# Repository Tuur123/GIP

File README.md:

# GIP
Luchtkwaliteit

Geïntegreede proef van Arthur d'Hooge en Ruben Socquet

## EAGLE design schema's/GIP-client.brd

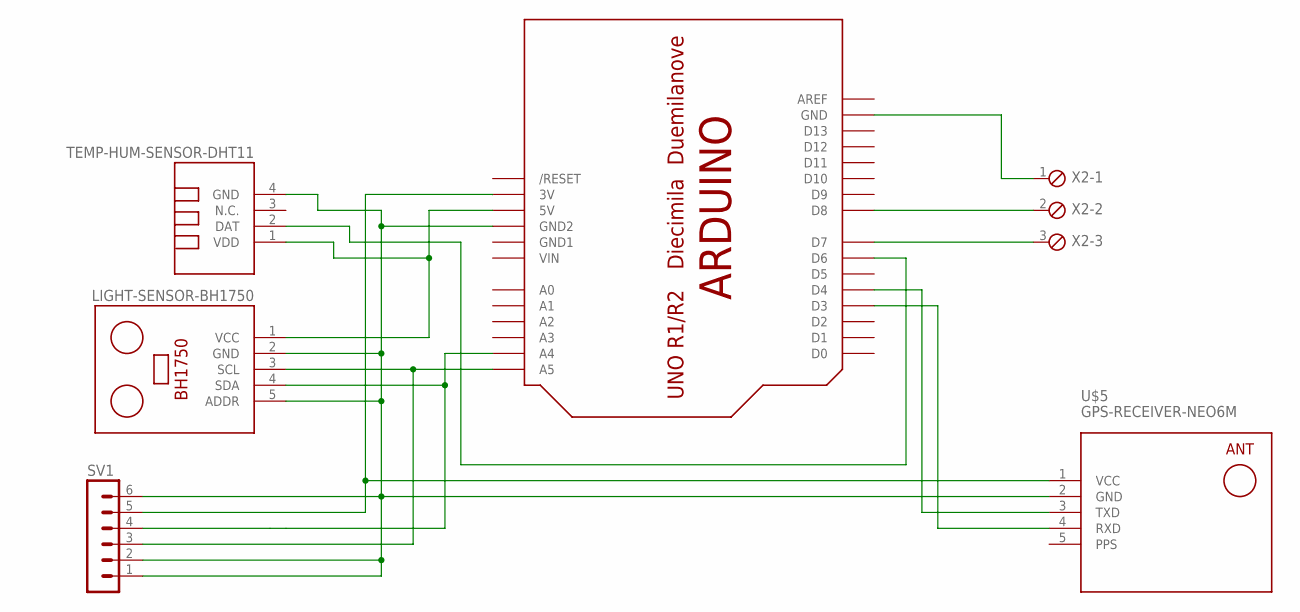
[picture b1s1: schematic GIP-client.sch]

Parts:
SV1: MA06-1
U$2: ARDUINO-BPLACE
U$3: TEMP-HUM-SENSOR-DHT11
U$4: LIGHT-SENSOR-BH1750
U$5: GPS-RECEIVER-NEO6M
X2: MPT3; 3POL254

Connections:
GND1: U$2.GND1
unnamed: U$2.GND, X2.1
unnamed: U$2.D8, X2.2
unnamed: U$2.D7, X2.3
unnamed: SV1.1, SV1.2, SV1.6, U$2.GND2, U$3.4 (GND), U$4.2 (GND), U$4.5 (ADDR), U$5.2 (GND)
unnamed: U$2.D6, U$3.2 (DAT)
unnamed: SV1.4, U$2.A4, U$4.4 (SDA)
unnamed: SV1.3, U$2.A5, U$4.3 (SCL)
unnamed: U$2.5V, U$3.1 (VDD), U$4.1 (VCC)
unnamed: SV1.5, U$2.3V, U$5.1 (VCC)
unnamed: U$2.D4, U$5.3 (TXD)
unnamed: U$2.D3, U$5.4 (RXD)
PPS: U$5.5 (PPS)
VIN: U$2.VIN

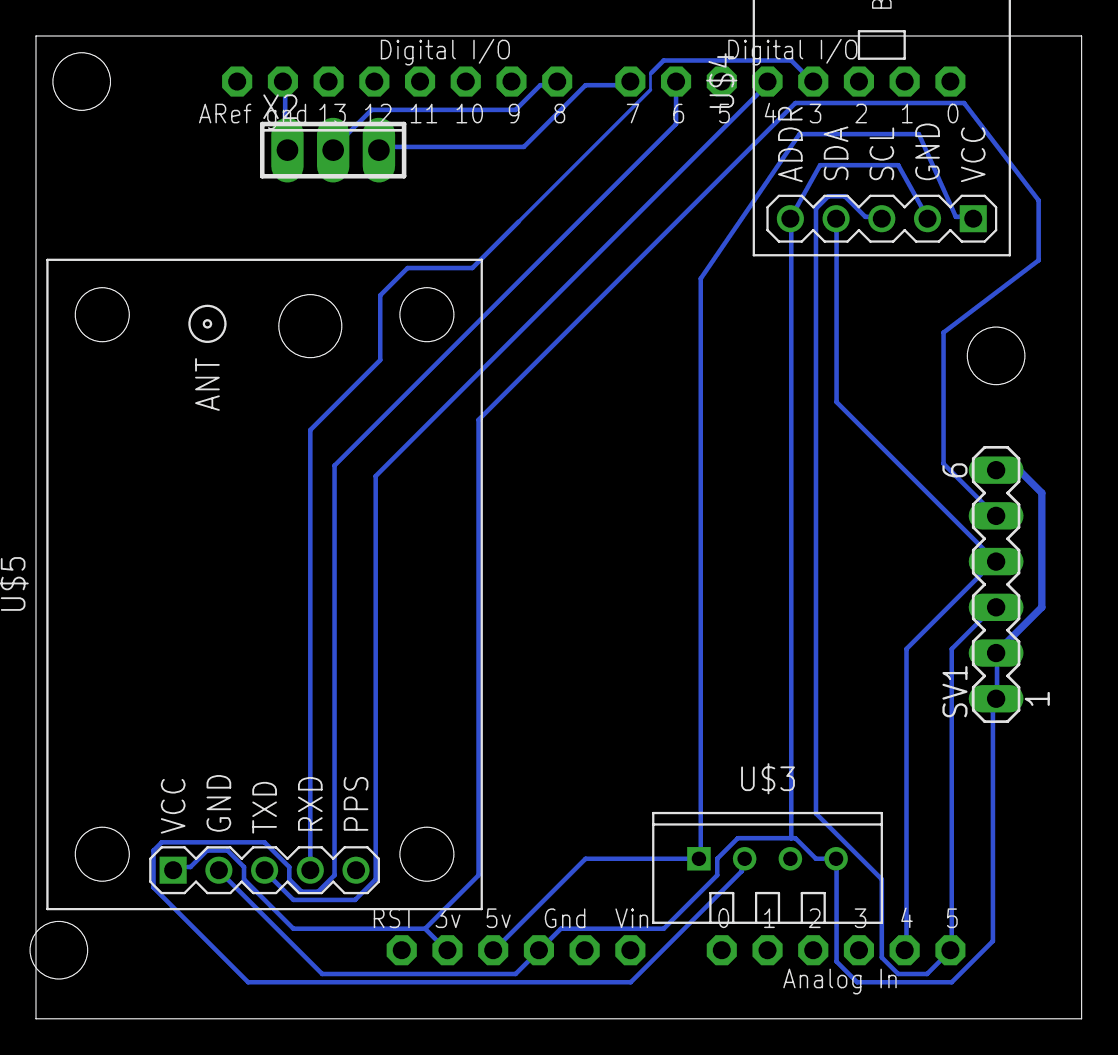
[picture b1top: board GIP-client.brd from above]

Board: 2 copper layers, 58.1 x 54.6 mm, 6 parts (0 on the bottom side), 11 nets.

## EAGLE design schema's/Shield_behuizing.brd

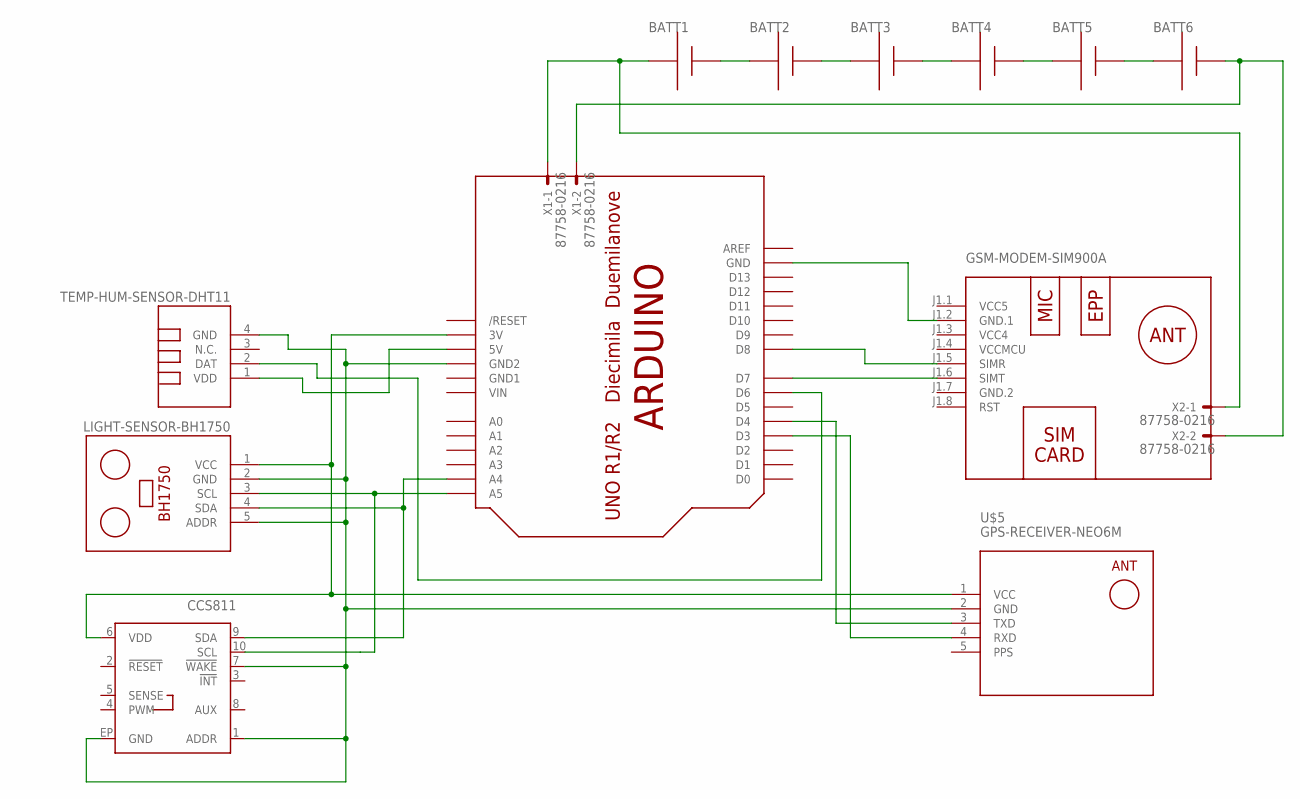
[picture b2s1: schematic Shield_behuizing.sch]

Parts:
BATT1, BATT2, BATT3, BATT4, BATT5, BATT6: AAA; 12BH412
U1: CCS811; LGA10
U$1: GSM-MODEM-SIM900A
U$2: ARDUINO-BPLACE
U$3: TEMP-HUM-SENSOR-DHT11
U$4: LIGHT-SENSOR-BH1750
U$5: GPS-RECEIVER-NEO6M
X1, X2: 87758-0216

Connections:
GND1: U$2.GND1
GND.2: U$1.J1.7 (GND.2)
unnamed: U$1.J1.2 (GND.1), U$2.GND
unnamed: U$1.J1.5 (SIMR), U$2.D8
unnamed: U$1.J1.6 (SIMT), U$2.D7
unnamed: BATT1.+, BATT2.-
unnamed: U1.1 (ADDR), U1.7 (!WAKE!), U1.EP (GND), U$2.GND2, U$3.4 (GND), U$4.2 (GND), U$4.5 (ADDR), U$5.2 (GND)
unnamed: U$2.D6, U$3.2 (DAT)
unnamed: U1.9 (SDA), U$2.A4, U$4.4 (SDA)
unnamed: U1.10 (SCL), U$2.A5, U$4.3 (SCL)
unnamed: U$2.5V, U$3.1 (VDD)
unnamed: BATT2.+, BATT3.-
unnamed: BATT3.+, BATT4.-
unnamed: BATT4.+, BATT5.-
unnamed: BATT5.+, BATT6.-
unnamed: U1.6 (VDD), U$2.3V, U$4.1 (VCC), U$5.1 (VCC)
unnamed: U$2.D4, U$5.3 (TXD)
unnamed: BATT1.-, X1.1, X2.1
unnamed: BATT6.+, X1.2, X2.2
unnamed: U$2.D3, U$5.4 (RXD)
PPS: U$5.5 (PPS)
VCC4: U$1.J1.3 (VCC4)
VCC5: U$1.J1.1 (VCC5)
VCCMCU: U$1.J1.4 (VCCMCU)
VIN: U$2.VIN

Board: 2 copper layers, 14 parts (0 on the bottom side), 18 nets, no tracks yet.

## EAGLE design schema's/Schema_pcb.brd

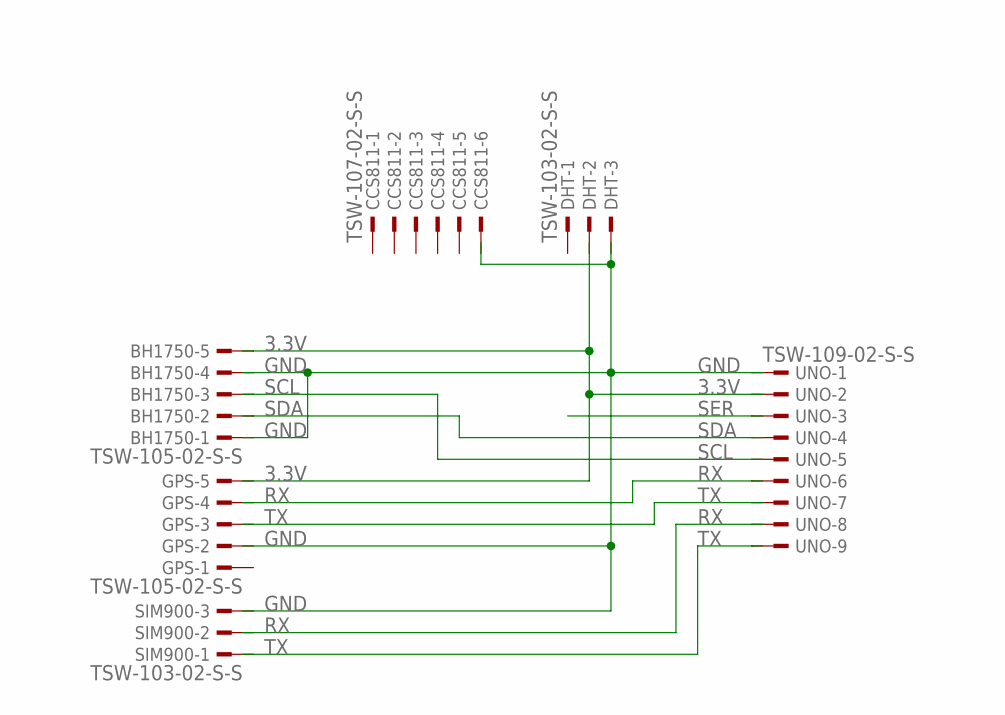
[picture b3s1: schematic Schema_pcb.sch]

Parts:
BH1750: TSW-105-02-S-S
CCS811: TSW-107-02-S-S
DHT: TSW-103-02-S-S
GPS: TSW-105-02-S-S
SIM900: TSW-103-02-S-S
UNO: TSW-109-02-S-S

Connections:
3.3V: BH1750.5, UNO.2
GND: BH1750.1, BH1750.4, UNO.1
RX: UNO.6, UNO.8
SCL: BH1750.3, UNO.5
SDA: BH1750.2, UNO.4
SER: UNO.3
TX: UNO.9

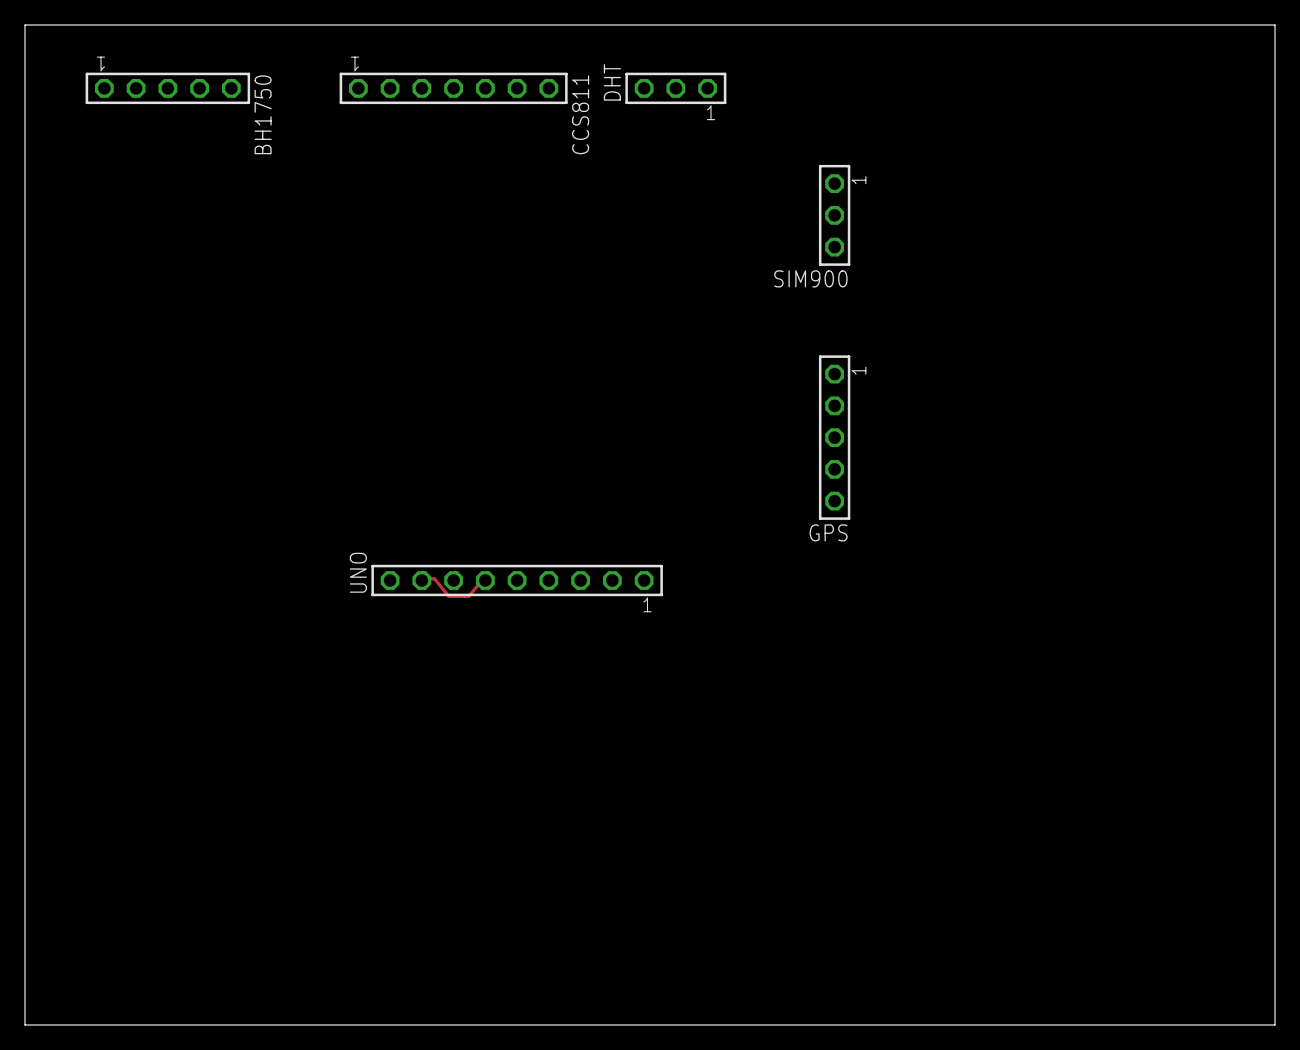
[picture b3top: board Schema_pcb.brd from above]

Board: 2 copper layers, 100.0 x 80.0 mm, 6 parts (0 on the bottom side), 5 nets.

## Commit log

2018-10-23 Create Sensors
2018-10-26 Dt-fout
2018-10-26 C02 Sensor
2018-10-26 Create humidity en temp sensor
2018-11-05 netwerkdiagram + het eigenlijke werk
2018-11-19 Bijgewerkt en afgedrukt
2018-11-19 bijgwerkt (bestellijst)
2018-11-20 Software toegevoegd
2018-12-17 alles bijgewerkt
    eigenlijke werk: def studie + detail ontwerp
    inhoudsopgave aangebracht
2018-12-17 logboek
    ik heb het logboek ineens mee in de bundel gestoken
    makkelijker om in te vullen
2018-12-26 Visual Studio project voor website toegevoegd
2018-12-26 Database toegevoegd
    Om data gebruikers en meetwaarde etc. te bewaren
2018-12-26 data listener toegevoegd
    de listener zal luisteren naar data van meettoestel op een specifieke poort en zal deze in de database zetten
2018-12-26 usings console app
    usings toegevoegd
2019-01-03 Create server side
2019-01-06 Lichtsensor sketch
2019-01-07 Bundel nu met versie nummers
    Als we nu tegelijk aan die bundel werke kunne we de elkaars werk ni per ongeluk weg doen da leek mij wel goe idee om me nummers te werke
2019-01-08 begin website gemaakt
    moet nog veeel aan gedaan worden
2019-01-08 AA batterijen toegevoegd
2019-01-08 website al wat mooier gemaakt
2019-01-08 website verder uitgewerkt, klasse toegevoegd om database te beheren
2019-01-08 methodes database
2019-01-08 Add files via upload
    sensoren uitgebreider toegevoegd aan de bundel. CO² sensor WERKT NIET! Dus nog niet toegevoegd
2019-01-09 schrijffoutjess en al stukje software uitgediept
2019-01-10 C02 sensor gefixtttt
    ge moest blijkbaar ook Wire.h toevoegen
2019-01-10 Bundel is af kijk t nog ff na op schrijffouten enzo en dan moogde t afdrukke zeker
2019-01-10 Add files via upload
    nog enkele aanpassingen gedaan, vitale 8 toegevoegd
2019-01-11 schema's en libraries
2019-01-11 schemas
2019-01-11 brol verwijdert
2019-01-12 Database.cs klasse uitgewerkt, website uitgewerkt
    website heeft nu een registreer pagina, user worden in database gezet, login methode is gemaakt. het enige voor de website wat nog moet gebeuren is data van sensors erop zetten en kaart inorde brengen
2019-01-12 update database
2019-01-12 sensormetingen + gps werken samen: andere code gebruikt voor gps
2019-01-14 Dit is de server app
2019-01-15 locatiegeg aangepast
2019-01-15 javascript gmaps toegevoegd
2019-01-15 db klasse voor server verbeterd
2019-01-15 database klasse voor website is aff
2019-01-15 vanalles
2019-01-16 ppt aangepast
2019-01-16 Kan jij de GIP-server.zip runnen op je pc aub
2019-01-16 Klein dingetje toegevoegd in Home.aspx.cs moet je wss wel terug verwijderen maar anders kon ik niet testen zorry
2019-01-17 Deze is zeker de werkende
2019-01-17 Tcplistener methode aangepast
2019-01-17 error.message ipv error.tostring gebruiken
    geeft meer detail over error
2019-01-22 website inorde brengen
    + beetje javascript
2019-01-23 bug gefixt
    was typ foutje
2019-02-05 website
2019-02-05 website opnief make
2019-02-10 Layout verder aangepast
2019-02-18 poging tot animaties met css
2019-02-19 map toegevoegd
2019-02-19 website map
2019-02-19 nieuwe layout
2019-02-22 buttons gefixed
2019-02-22 pcb gemaakt
2019-02-22 Pcb afgemaakt
2019-02-22 website widget en aanpassingen
2019-02-26 over ons toegevoegd
2019-02-26 over oons
2019-02-27 over ons
2019-02-27 behuizing afgemaakt
2019-02-27 map en stufff
2019-02-27 gwn aardbevingen erin gekiet
2019-02-28 beetje kloten met geojson niet verder geraakt HELP!!!
2019-03-01 bezig aan grafieken
2019-03-01 graphs
2019-03-01 Bezig met JSON uit te zoeken
2019-03-08 dit is zo moeilijk fml kwil dood
2019-03-10 verder aan json gewerkt. We are really close now.
2019-03-12 probleem met database gefixt
2019-03-13 OPLOSSING VOOR DE MARKESS
    in javascript maken we een for loop en voila probleem gefixt
2019-03-13 teste
2019-03-13 sike i lied
2019-03-13 kleine stapjes
2019-03-14 Verschillende problemen opgelost
    GeoJSON werkt; hiep hiep hoera
    Nu moeten we manier zoeken om van client side JavaScript de json files van de server te halen.
2019-03-14 sd komt eraan
2019-03-15 ik irriteerde me aan die \n
    lijn 139 in Home.aspx
2019-03-15 website testen Grafiken werken NIET meer?
2019-03-16 SD-kaart uploader bij website toegevoegd WERKT! + volledige Arduino code
2019-03-19 code nagekeken
    er moeten veiligheden ingebouwd worden bij de file upload, anders is sql injection een gevaar en kan er bs in de db gezet worden. server kan ook compleet crashen
2019-03-19 bezig met api te maken
2019-03-19 api werkt blijkbaar niet in een gewoon asp project zoals de onze
2019-03-19 Ik heb tinne haar commentaar allemaal aann gepast en die bundel mooi gemaakt echt KKKKKAAANKER zooi
    IK WORD HEELEMAAL WAUW
2019-03-20 code sd kaart verbeterd
    bestand word niet permanent op server bewaard, blijft in memory
2019-03-20 emc toe aan het voegen
2019-03-21 kleine wijzigingen
    voor api
2019-03-21 foto bunndel
2019-03-21 client side in bundel gezet
2019-03-21 pcb erin gezet
2019-03-21 af denk ik
2019-03-21 pdf ook ineens toegevoegd
2019-03-22 webmethod gebruiken voor query
2019-03-22 webmethods
2019-03-22 Update GIP-PPT-2_RS_AdH.pptx
    veiligheids punt toegevoegd
2019-03-22 finale ppt
2019-03-26 lichtsersor werkt niet linrary probleem
2019-03-27 Rare dingen ?
2019-03-27 markers werkennn
    ye boii
2019-03-27 arduiuno tijd gps
2019-03-27 het werkt. Ik weet niet precies aan wat het lag
2019-03-27 Het werkt via sd en 4g met tijd
2019-03-28 website gepublished op iis
2019-03-28 gerber files voor pcb
2019-03-28 pcb besteld
2019-03-28 nog nen tijd lopen kutten :disappointed_relieved:
2019-04-01 error handling data_listener
2019-04-13 proberen charts te laten scrollen
2019-04-15 mooiere grafieken gemaakt met Chart.js
    javascript charts in plaats van lelijke asp charts gemaakt, nieuwe klasse gemaakt binnen Database.cs om chart data te bewaren
2019-04-16 sliders toegevoegd om grafieken te laten scrollen
2019-04-20 to do list aangevuld, ik zal de website mooier maken.
2019-04-22 hoofdstukje in bundel gezet
2019-04-23 snelheid meten controleer naukeurigheid
2019-04-23 vanallees
    - check bij de listener gemaakt zodat slechte data niet in database komt
    - arduino code nog wat cleaner gemaakt
2019-04-24 bundeltjee
2019-04-26 to do
2019-04-26 js verbeter
2019-04-26 buundel
2019-04-30 footer toegevoegd
2019-05-03 bundel nagezien, header info toegevoegd
2019-05-04 update sim900 andere methode werkte niet
2019-05-04 communicatie gefixt Website was aangepast
2019-05-04 bundel en to do
2019-05-05 arduino code ziet er goed uit
2019-05-06 TIJDELIJKE UPLOAD BEN NOG NIET KLAAR!
2019-05-06 ga u gang
2019-05-06 oh nee vergeten te saven
    prank
2019-05-07 GPS LIB
2019-05-07 bundel
2019-05-07 laatste aanp. is klaar! ;)
2019-05-07 ip server in arduino code aangepast naar hostname
2019-05-07 goed nieuws: data uit db verwijderen lukt
    slecht nieuws: alle meetwaardes zijn foetsjie :beers: )
2019-05-08 pdf bundel en bundel word
2019-05-08 nog wijzigingen gedaan in de bundel verbeter met mama
2019-05-09 Dit heb ik geüpload in de projectmap uploadzone
2019-05-28 test
2019-05-28 uploaden werkt weer
2019-05-29 kijk socket test om server te simuleren
2019-05-31 De code om te bepalen wanneer de gps geen connectie heeft werkt niet
2019-05-31 code database.cs toegevoegd maar het geheel moet nog getest worden
2019-05-31 over ons vervolledigd, db upload gefixd voor coordinaten
    email aan footer toegevoegd, moet je maar is checken vond ik best cool
2019-06-01 Bij toevoegen data aan de db word de gemeente van meting bepaald en in db gezet
    db_listener klasse verwijdert, data word in listener.cs in db gezet. code voor api bevraging staat ook in listener.cs en in database.cs. TODO: bij client Javascript sorteren op gemeentes
2019-06-01 webmethod returned nu ook de gemeente in json string
2019-06-03 gps controle dat niet werkte weg gedaan
2019-06-04 website kleine vernaderingen
2019-06-04 Definitieve versie
2022-06-22 Bump Newtonsoft.Json in /Website/Website_GIP/Website_GIP
    Bumps [Newtonsoft.Json](https://github.com/JamesNK/Newtonsoft.Json) from 12.0.1 to 13.0.1.
    - [Release notes](https://github.com/JamesNK/Newtonsoft.Json/releases)
    - [Commits](https://github.com/JamesNK/Newtonsoft.Json/compare/12.0.1...13.0.1)
    ---
    updated-dependencies:
    - dependency-name: Newtonsoft.Json
2022-06-22 Bump Newtonsoft.Json in /Website/Website_GIP/Data_Listener
    Bumps [Newtonsoft.Json](https://github.com/JamesNK/Newtonsoft.Json) from 12.0.1 to 13.0.1.
    - [Release notes](https://github.com/JamesNK/Newtonsoft.Json/releases)
    - [Commits](https://github.com/JamesNK/Newtonsoft.Json/compare/12.0.1...13.0.1)
    ---
    updated-dependencies:
    - dependency-name: Newtonsoft.Json
2022-12-08 Bump Newtonsoft.Json in /Website/Website_GIP/Website_GIP
    Bumps [Newtonsoft.Json](https://github.com/JamesNK/Newtonsoft.Json) from 12.0.1 to 13.0.2.
    - [Release notes](https://github.com/JamesNK/Newtonsoft.Json/releases)
    - [Commits](https://github.com/JamesNK/Newtonsoft.Json/compare/12.0.1...13.0.2)
    ---
    updated-dependencies:
    - dependency-name: Newtonsoft.Json
2022-12-08 Bump Newtonsoft.Json in /Website/Website_GIP/Data_Listener
    Bumps [Newtonsoft.Json](https://github.com/JamesNK/Newtonsoft.Json) from 12.0.1 to 13.0.2.
    - [Release notes](https://github.com/JamesNK/Newtonsoft.Json/releases)
    - [Commits](https://github.com/JamesNK/Newtonsoft.Json/compare/12.0.1...13.0.2)
    ---
    updated-dependencies:
    - dependency-name: Newtonsoft.Json

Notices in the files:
parts and their libraries:
diy-modules: Released under the Creative Commons Attribution 4.0 International License: http://creativecommons.org/licenses/by/4.0
